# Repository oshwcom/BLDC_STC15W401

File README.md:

BLDC_STC15W401AS
===========================
一个低成本的12V无刷直流（BLDC）电机的驱动模块。

------

|Author|刘焕银|
|---|---
|E-mail|25199527@qq.com

------

## 目录
* [目标](#目标)
* [功能](#功能)
* [原理图](#原理图)

------

### 目标
    完成一款低成本（人民币7元以下）的BLDC驱动电路。  

------

### 功能
1. 驱动12V的BLDC电机，最大输出功率15瓦左右。
2. 可以正反转。
3. 转速800~1500转。

------

### 原理图
    V0.2版原理图。  修订了MOSFET的型号，多加了一种替代封装（SOT23和TO252)。

------

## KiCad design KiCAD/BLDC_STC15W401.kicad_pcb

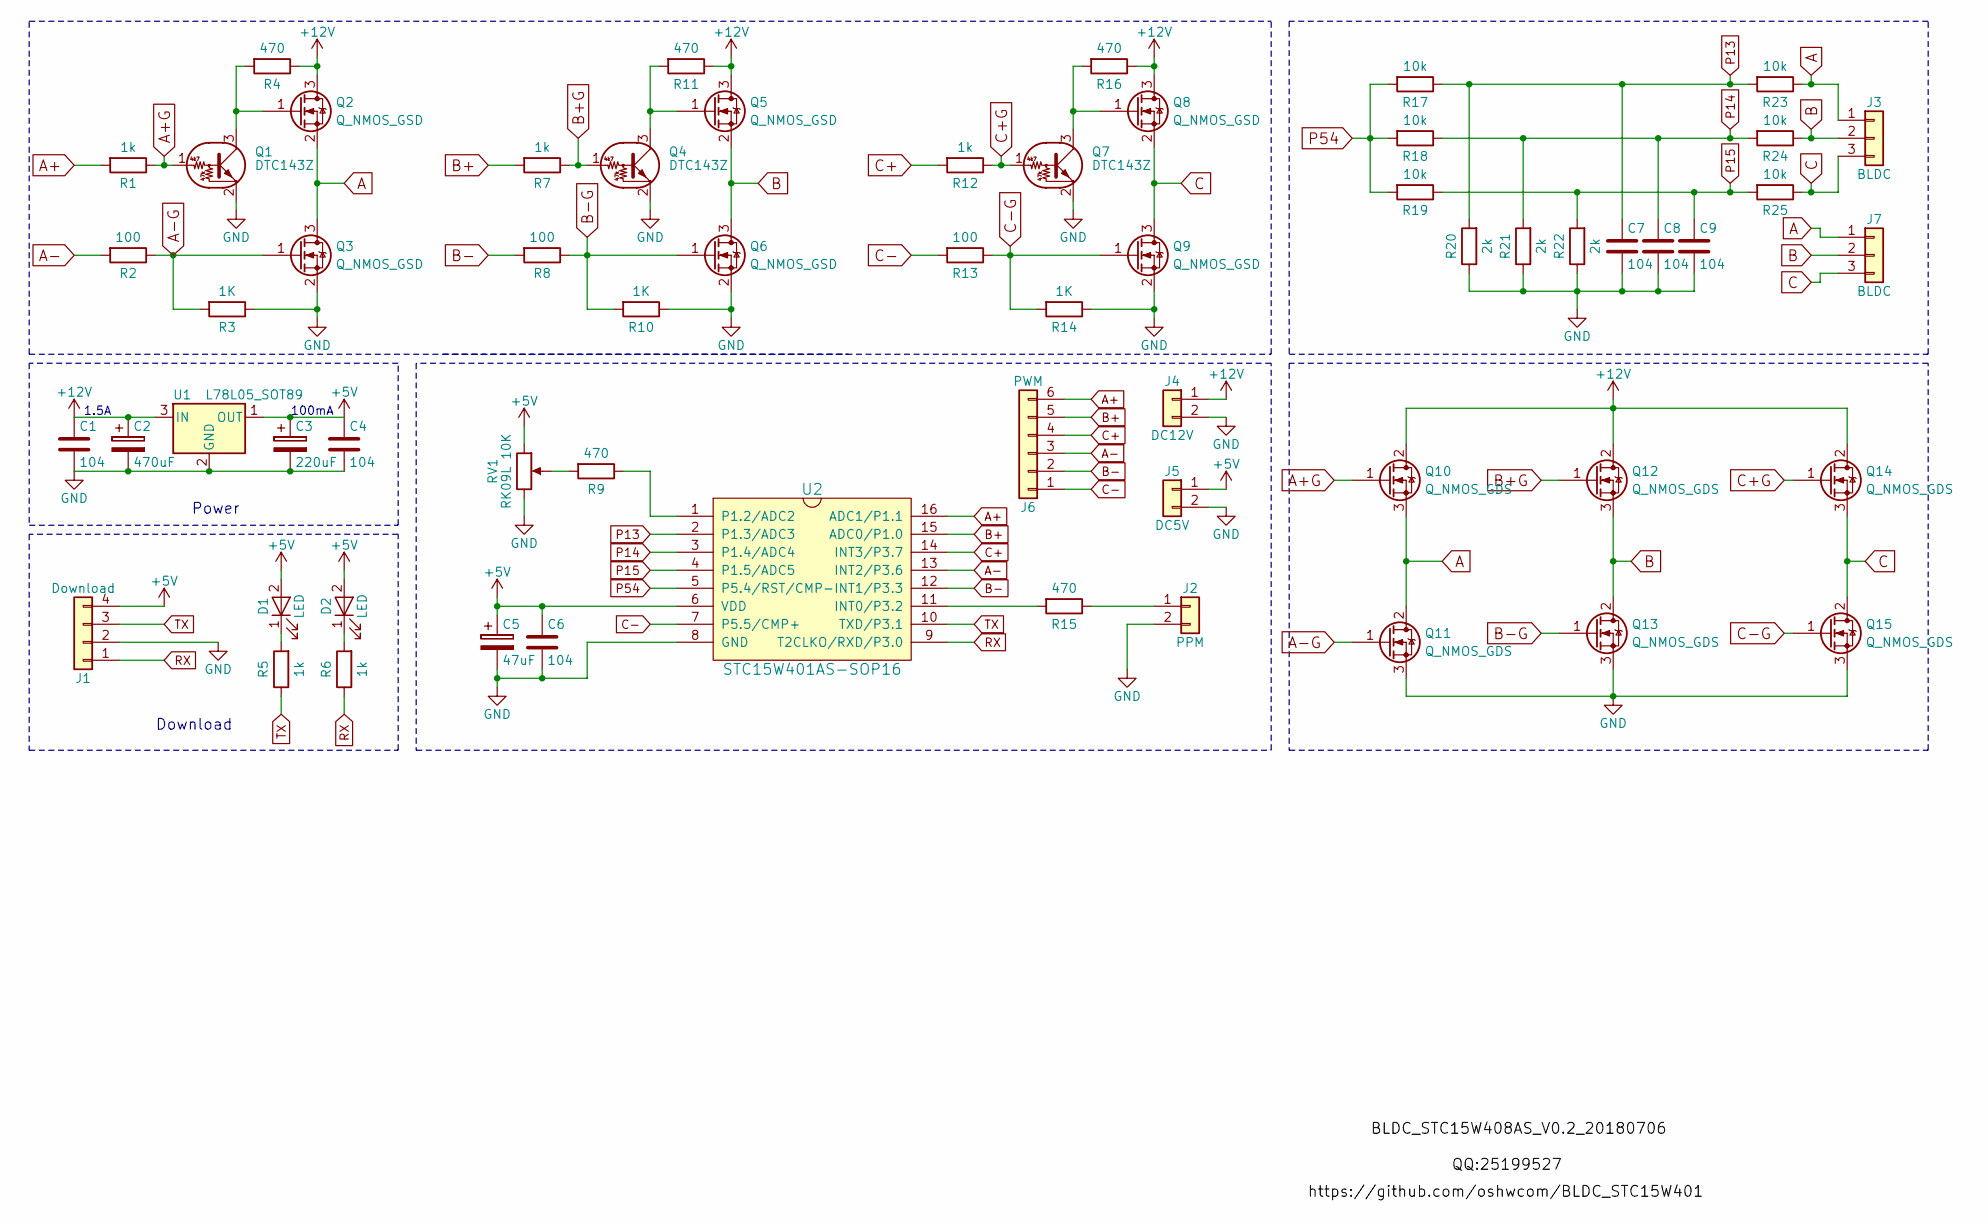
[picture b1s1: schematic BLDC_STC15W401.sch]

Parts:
C1, C4, C6, C7, C8, C9: 104; C_0805_HandSoldering
C2: 470uF; CP_Radial_D6.3mm_P2.50mm
C3: 220uF; CP_Radial_D5.0mm_P2.00mm
C5: 47uF; CP_Radial_D4.0mm_P1.50mm
D1, D2: LED; LED_0805_HandSoldering
J1: Download; JST_XH_B04B-XH-A_04x2.50mm_Straight
J2: PPM; JST_XH_B02B-XH-A_02x2.50mm_Straight
J3: BLDC; JST_XH_B03B-XH-A_03x2.50mm_Straight
J4: DC12V; JST_XH_B02B-XH-A_02x2.50mm_Straight
J5: DC5V; JST_XH_B02B-XH-A_02x2.50mm_Straight
J6: PWM; JST_XH_B06B-XH-A_06x2.50mm_Straight
J7: BLDC; JST_VH_B5P-VH-B_5A3x3.96mm_Vertical
Q1, Q4, Q7: DTC143Z; SOT-23_Handsoldering
Q2, Q3, Q5, Q6, Q8, Q9: Q_NMOS_GSD; SOT-23_Handsoldering
Q10, Q11, Q12, Q13, Q14, Q15: Q_NMOS_GDS; TO-252-2
R1, R5, R6, R7, R12: 1k; R_0805_HandSoldering
R2, R8, R13: 100; R_0805_HandSoldering
R3, R10, R14: 1K; R_0805_HandSoldering
R4, R9, R11, R15, R16: 470; R_0805_HandSoldering
R17, R18, R19, R23, R24, R25: 10k; R_0805_HandSoldering
R20, R21, R22: 2k; R_0805_HandSoldering
RV1: RK09L 10K; Potentiometer_Alps_RK09L_Sleve_Single_Horizontal
U1: L78L05_SOT89; SOT-89-3_Handsoldering
U2: STC15W401AS-SOP16; SOIC-16_3.9x9.9mm_Pitch1.27mm

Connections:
+5V: C3.1, C4.1, C5.1, C6.1, D1.2 (A), D2.2 (A), J1.4, J5.1, RV1.1, U1.1 (OUT), U2.6 (VDD)
+12V: C1.1, C2.1, J4.1, Q2.3 (D), Q5.3 (D), Q8.3 (D), Q10.2 (D), Q12.2 (D), Q14.2 (D), R4.1, R11.1, R16.1, U1.3 (IN)
A: J3.1, J7.1, Q2.2 (S), Q3.3 (D), Q10.3 (S), Q11.2 (D), R23.1
A+: J6.6, R1.2, U2.16 (ADC1/P1.1)
A+G: Q1.1 (B), Q10.1 (G), R1.1
A-: J6.3, R2.2, U2.13 (INT2/P3.6)
A-G: Q3.1 (G), Q11.1 (G), R2.1, R3.2
B: J3.2, J7.2, Q5.2 (S), Q6.3 (D), Q12.3 (S), Q13.2 (D), R24.1
B+: J6.5, R7.2, U2.15 (ADC0/P1.0)
B+G: Q4.1 (B), Q12.1 (G), R7.1
B-: J6.2, R8.2, U2.12 (INT1/P3.3)
B-G: Q6.1 (G), Q13.1 (G), R8.1, R10.2
C: J3.3, J7.3, Q8.2 (S), Q9.3 (D), Q14.3 (S), Q15.2 (D), R25.1
C+: J6.4, R12.2, U2.14 (INT3/P3.7)
C+G: Q7.1 (B), Q14.1 (G), R12.1
C-: J6.1, R13.2, U2.7 (P5.5/CMP+)
C-G: Q9.1 (G), Q15.1 (G), R13.1, R14.2
GND: C1.2, C2.2, C3.2, C4.2, C5.2, C6.2, C7.2, C8.2, C9.2, J1.2, J2.2, J4.2, J5.2, Q1.2 (E), Q3.2 (S), Q4.2 (E), Q6.2 (S), Q7.2 (E), Q9.2 (S), Q11.3 (S), Q13.3 (S), Q15.3 (S), R3.1, R10.1, R14.1, R20.1, R21.1, R22.1, RV1.3, U1.2 (GND), U2.8 (GND)
unnamed: D1.1 (K), R5.2
unnamed: D2.1 (K), R6.2
unnamed: J2.1, R15.1
unnamed: Q1.3 (C), Q2.1 (G), R4.2
unnamed: Q4.3 (C), Q5.1 (G), R11.2
unnamed: Q7.3 (C), Q8.1 (G), R16.2
unnamed: R9.1, U2.1 (P1.2/ADC2)
unnamed: R9.2, RV1.2
unnamed: R15.2, U2.11 (INT0/P3.2)
P13: C7.1, R17.1, R20.2, R23.2, U2.2 (P1.3/ADC3)
P14: C8.1, R18.1, R21.2, R24.2, U2.3 (P1.4/ADC4)
P15: C9.1, R19.1, R22.2, R25.2, U2.4 (P1.5/ADC5)
P54: R17.2, R18.2, R19.2, U2.5 (P5.4/RST/CMP-)
RX: J1.1, R6.1, U2.9 (T2CLKO/RXD/P3.0)
TX: J1.3, R5.1, U2.10 (TXD/P3.1)

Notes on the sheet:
Power
Download
100mA
1.5A

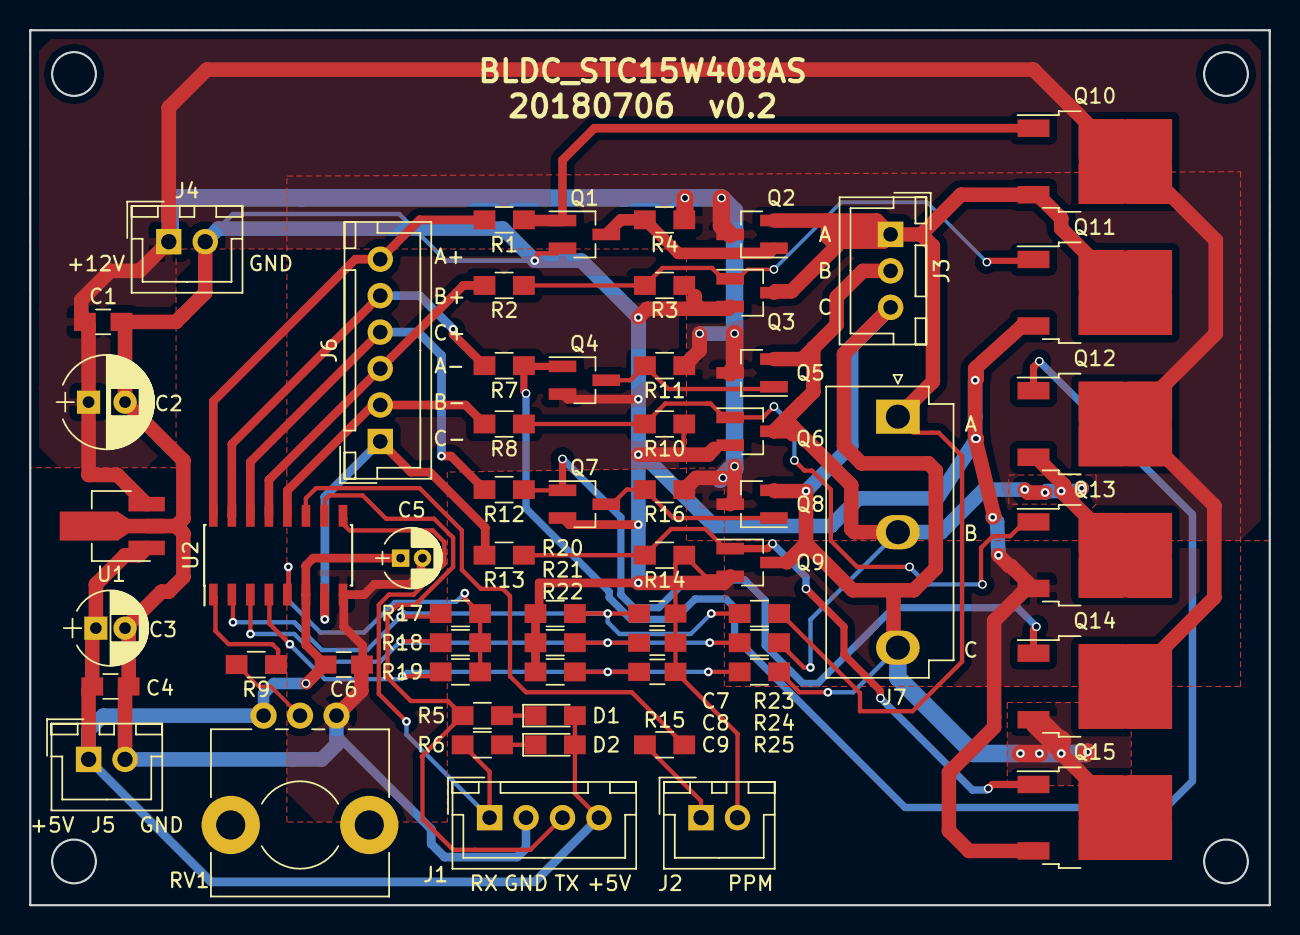
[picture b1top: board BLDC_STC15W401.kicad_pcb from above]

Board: 2 copper layers, 85.0 x 60.0 mm, 61 parts (0 on the bottom side), 33 nets.

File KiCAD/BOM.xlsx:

Id | 位号 | 封装 | 数量 | 描述
1 | J4 | JST_XH_B02B-XH-A_02x2.50mm_Straight | 1 | DC12V
2 | C1,C4,C6,C7,C8,C9 | C_0805_HandSoldering | 6 | 104
3 | C2 | CP_Radial_D6.3mm_P2.50mm | 1 | 470uF
4 | C3 | CP_Radial_D5.0mm_P2.00mm | 1 | 220uF
5 | C5 | CP_Radial_D4.0mm_P1.50mm | 1 | 47uF
6 | D1,D2 | LED_0805_HandSoldering | 2 | LED
7 | J1 | JST_XH_B04B-XH-A_04x2.50mm_Straight | 1 | Download
8 | J2 | JST_XH_B02B-XH-A_02x2.50mm_Straight | 1 | PPM
9 | J3 | JST_XH_B03B-XH-A_03x2.50mm_Straight | 1 | BLDC
10 | Q1,Q4,Q7 | SOT-23_Handsoldering | 3 | DTC143Z
11 | Q2,Q5,Q8 | SOT-23_Handsoldering | 3 | Q_PMOS_GSD
12 | Q3,Q6,Q9 | SOT-23_Handsoldering | 3 | Q_NMOS_GSD
13 | R1,R5,R6,R7,R12 | R_0805_HandSoldering | 5 | 1k
14 | R2,R8,R13 | R_0805_HandSoldering | 3 | 100
15 | R3,R10,R14 | R_0805_HandSoldering | 3 | 18K
16 | R4,R9,R11,R15,R16 | R_0805_HandSoldering | 5 | 470
17 | R17,R18,R19,R23,R24,R25 | R_0805_HandSoldering | 6 | 10k
18 | R20,R21,R22 | R_0805_HandSoldering | 3 | 2k
19 | RV1 | Potentiometer_Alps_RK09L_Sleve_Single_Horizontal | 1 | RK09L 10K
20 | U1 | SOT-89-3_Handsoldering | 1 | L78L05_SOT89
21 | U2 | SOIC-16_3.9x9.9mm_Pitch1.27mm | 1 | STC15W401AS-SOP16
22 | J5 | JST_XH_B02B-XH-A_02x2.50mm_Straight | 1 | DC5V
23 | J6 | JST_XH_B06B-XH-A_06x2.50mm_Straight | 1 | PWM
24 | J7 | JST_VH_B5P-VH-B_5A3x3.96mm_Vertical | 1 | BLDC

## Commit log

2018-06-23 首次提交
2018-06-23 添加readme.txt和.gitignore文件
2018-06-23 Update readme.txt
    更改文件格式
2018-06-23 更新Readme。 更改报价资料
2018-06-23 增加说明文件
2018-06-23 更新说明文件
2018-06-23 删除多余文件
2018-06-23 更新描述文件
2018-06-23 添加产品图片
2018-07-06 添加BOM及N多MOSFET的datasheet
2018-07-06 添加V0.2的PCB设计
2018-07-06 添加软件代码，从飞控的PPM改成串口调速。
2018-07-06 添加原理图
2018-07-06 添加SVG格式原理图
2018-07-06 更新说明文档
